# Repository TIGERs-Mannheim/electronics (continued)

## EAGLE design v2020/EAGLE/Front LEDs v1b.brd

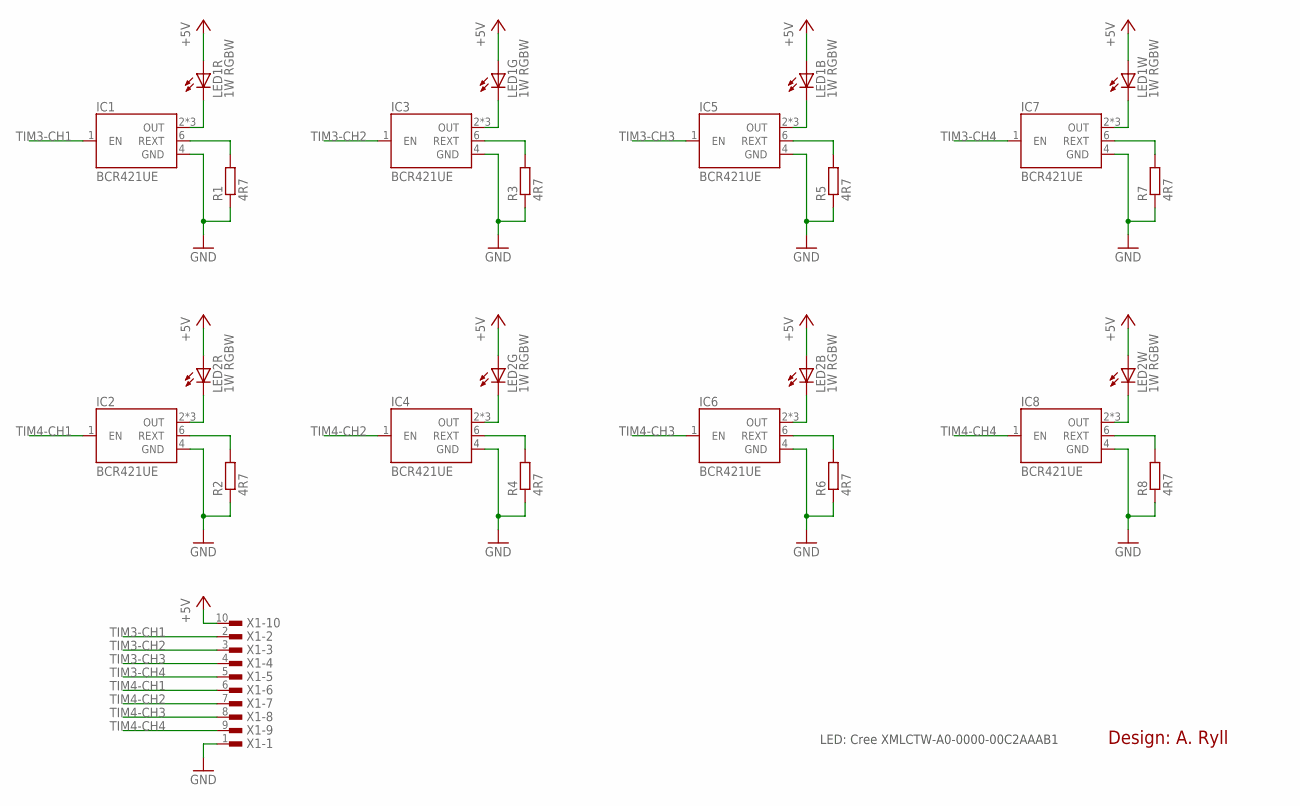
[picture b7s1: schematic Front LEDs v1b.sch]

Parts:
IC1, IC2, IC3, IC4, IC5, IC6, IC7, IC8: BCR421UE; SOT26
LED1, LED2: 1W RGBW; CREE-XLAMP; PARTNR XMLCTW-A0-0000-00C2AAAB1
R1, R2, R3, R4, R5, R6, R7, R8: 4R7; R0805
X1: TE-FPC-1MM-10H; TE-1-84952-0

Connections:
+5V: LED1.1 (A), LED1.2 (A), LED1.3 (A), LED1.4 (A), LED2.1 (A), LED2.2 (A), LED2.3 (A), LED2.4 (A), X1.10
GND: IC1.4 (GND), IC2.4 (GND), IC3.4 (GND), IC4.4 (GND), IC5.4 (GND), IC6.4 (GND), IC7.4 (GND), IC8.4 (GND), R1.1, R2.1, R3.1, R4.1, R5.1, R6.1, R7.1, R8.1, X1.1
unnamed: IC1.2 (OUT), IC1.3 (OUT), IC1.5 (OUT), LED1.8 (C)
unnamed: IC1.6 (REXT), R1.2
unnamed: IC3.2 (OUT), IC3.3 (OUT), IC3.5 (OUT), LED1.7 (C)
unnamed: IC3.6 (REXT), R3.2
unnamed: IC5.2 (OUT), IC5.3 (OUT), IC5.5 (OUT), LED1.6 (C)
unnamed: IC5.6 (REXT), R5.2
unnamed: IC7.2 (OUT), IC7.3 (OUT), IC7.5 (OUT), LED1.5 (C)
unnamed: IC7.6 (REXT), R7.2
unnamed: IC2.2 (OUT), IC2.3 (OUT), IC2.5 (OUT), LED2.8 (C)
unnamed: IC2.6 (REXT), R2.2
unnamed: IC4.2 (OUT), IC4.3 (OUT), IC4.5 (OUT), LED2.7 (C)
unnamed: IC4.6 (REXT), R4.2
unnamed: IC6.2 (OUT), IC6.3 (OUT), IC6.5 (OUT), LED2.6 (C)
unnamed: IC6.6 (REXT), R6.2
unnamed: IC8.2 (OUT), IC8.3 (OUT), IC8.5 (OUT), LED2.5 (C)
unnamed: IC8.6 (REXT), R8.2
TIM3-CH1: IC1.1 (EN), X1.2
TIM3-CH2: IC3.1 (EN), X1.3
TIM3-CH3: IC5.1 (EN), X1.4
TIM3-CH4: IC7.1 (EN), X1.5
TIM4-CH1: IC2.1 (EN), X1.6
TIM4-CH2: IC4.1 (EN), X1.7
TIM4-CH3: IC6.1 (EN), X1.8
TIM4-CH4: IC8.1 (EN), X1.9

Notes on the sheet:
Design: A. Ryll
LED: Cree XMLCTW-A0-0000-00C2AAAB1

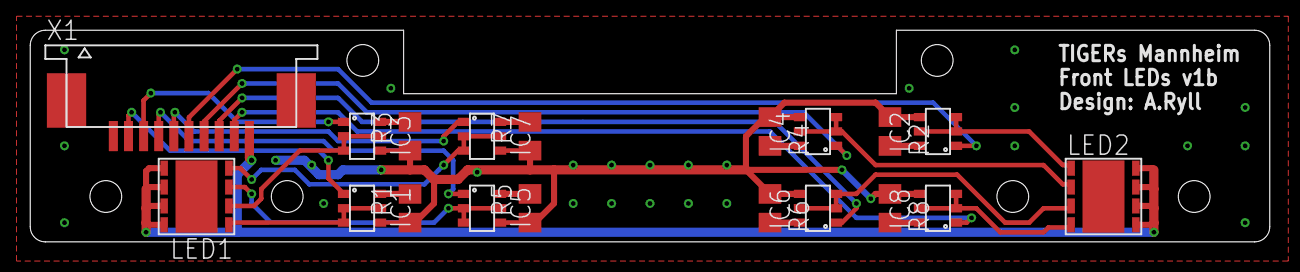
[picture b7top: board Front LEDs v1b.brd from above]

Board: 2 copper layers, 82.0 x 14.0 mm, 19 parts (0 on the bottom side), 26 nets.

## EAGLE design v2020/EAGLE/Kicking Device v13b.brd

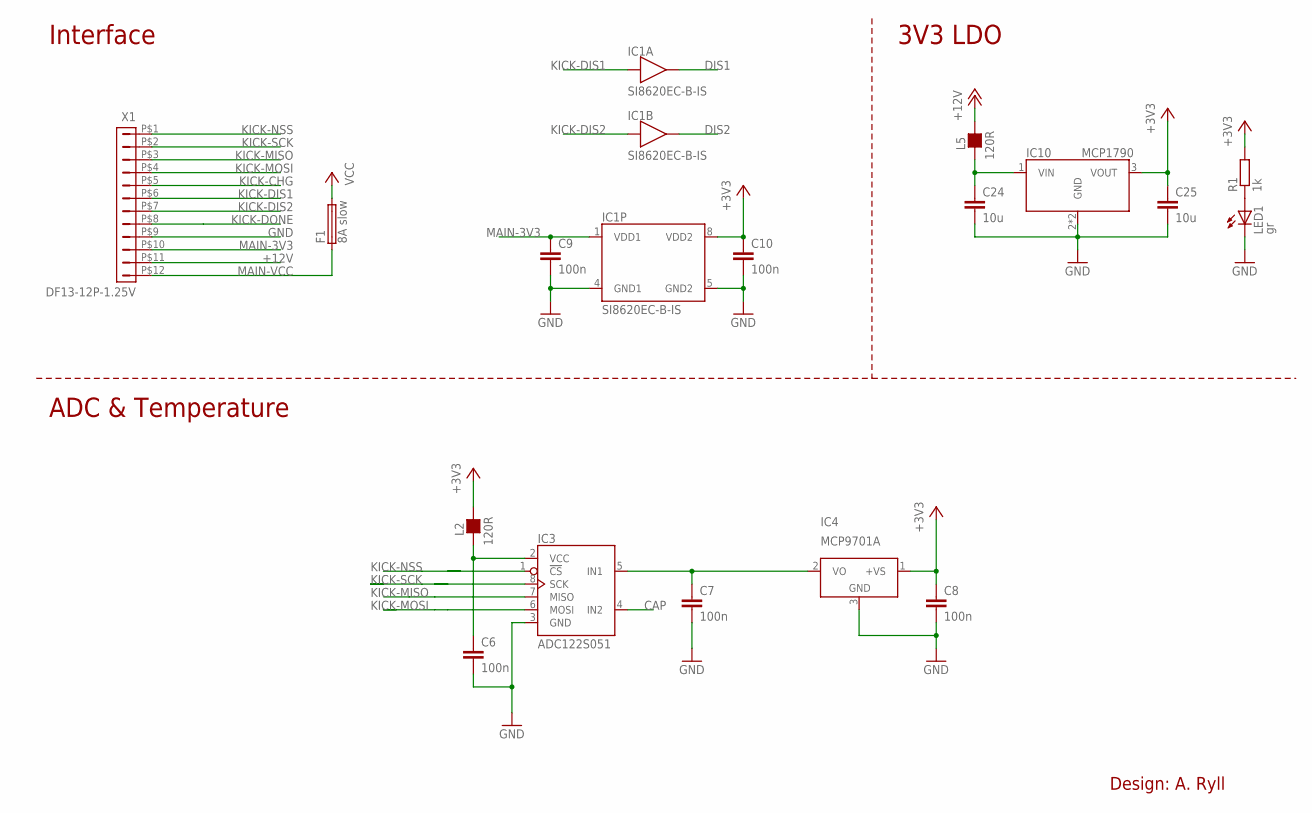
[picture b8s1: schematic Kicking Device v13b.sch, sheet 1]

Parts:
C6, C7, C8, C9, C10: 100n; C0603
C24, C25: 10u; C0603
F1: 8A slow; 1206
IC1: SI8620EC-B-IS; SOIC8N
IC3: ADC122S051; MSOP8
IC4: MCP9701A; SOT23
IC10: MCP1790; SOT223
L2, L5: 120R; L0603
LED1: gr; CHIP-LED0603
R1: 1k; R0603
X1: DF13-12P-1.25V; DF13C-12P-1.25V

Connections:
+3V3: C8.1, C10.1, C25.1, IC1.8 (VDD2), IC4.1 (+VS), IC10.3 (VOUT), L2.2, R1.2; also elsewhere on the board
+12V: L5.2, X1.P$11 (11); also elsewhere on the board
CAP: IC3.4 (IN2); also elsewhere on the board
DIS1: IC1.7 (OUT); also elsewhere on the board
DIS2: IC1.6 (OUT); also elsewhere on the board
GND: C6.2, C7.2, C8.2, C9.2, C10.2, C24.2, C25.2, IC1.4 (GND1), IC1.5 (GND2), IC3.3 (GND), IC4.3 (GND), IC10.2 (GND), IC10.4 (GND), LED1.C, X1.P$9 (9); also elsewhere on the board
KICK-CHG: X1.P$5 (5); also elsewhere on the board
KICK-DIS1: IC1.2 (IN), X1.P$6 (6)
KICK-DIS2: IC1.3 (IN), X1.P$7 (7)
KICK-DONE: X1.P$8 (8); also elsewhere on the board
KICK-MISO: IC3.7 (MISO), X1.P$3 (3)
KICK-MOSI: IC3.6 (MOSI), X1.P$4 (4)
KICK-NSS: IC3.1 (!CS), X1.P$1 (1)
KICK-SCK: IC3.8 (SCK), X1.P$2 (2)
MAIN-3V3: C9.1, IC1.1 (VDD1), X1.P$10 (10)
MAIN-VCC: F1.1, X1.P$12 (12)
unnamed: C24.1, IC10.1 (VIN), L5.1
unnamed: C6.1, IC3.2 (VCC), L2.1
unnamed: C7.1, IC3.5 (IN1), IC4.2 (VO)
unnamed: LED1.A, R1.1
VCC: F1.2; also elsewhere on the board

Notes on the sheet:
Interface
3V3 LDO
ADC & Temperature
Design: A. Ryll

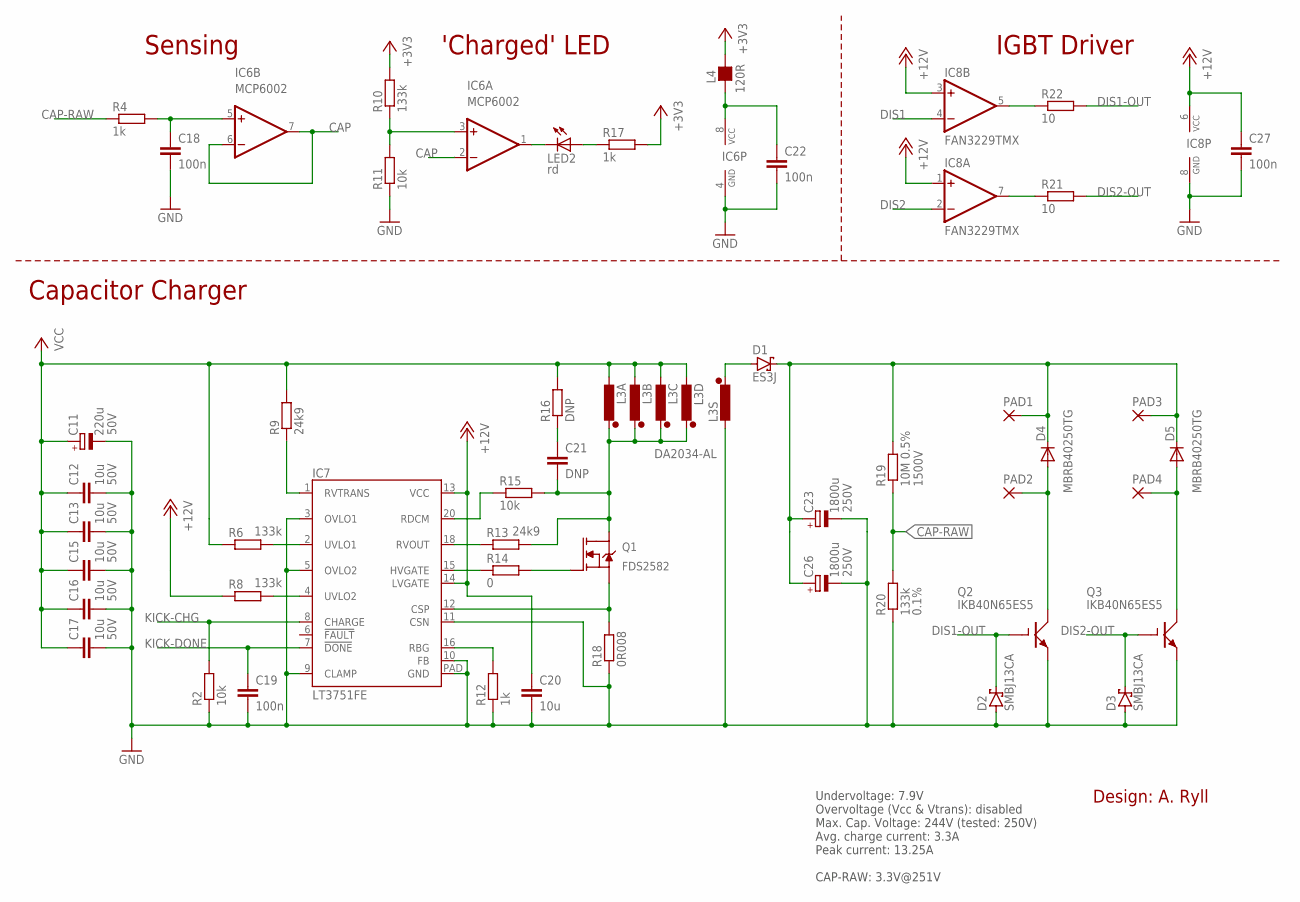
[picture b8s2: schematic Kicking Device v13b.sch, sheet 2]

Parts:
C11: 220u; PANASONIC_F; PARTNR EEEFT1H221AP
C12, C13, C15, C16, C17: 10u; C1210; PARTNR C3225X5R1H106M250AB
C18, C19, C22, C27: 100n; C0603
C20: 10u; C0603
C21: DNP; C0805
C23, C26: 1800u; EB35D
D1: ES3J; SMC
D2, D3: SMBJ13CA; SMB
D4, D5: MBRB40250TG; D2PAK
IC6: MCP6002; SOIC8N
IC7: LT3751FE; TSSOP20P
IC8: FAN3229TMX; SOIC8N
L3: DA2034-AL
L4: 120R; L0603
LED2: rd; CHIP-LED0603
PAD1, PAD2, PAD3, PAD4: WIREPAD2,54/1,0; 2,54/1,0
Q1: FDS2582; SOIC8N
Q2, Q3: IKB40N65ES5; D2PAK
R2, R11, R15: 10k; R0603
R4, R12, R17: 1k; R0603
R6, R8, R10, R20: 133k; R0603
R9, R13: 24k9; R0603
R14: 0; R1206
R16: DNP; R0805
R18: 0R008; R1206
R19: 10M 0.5%; R1206
R21, R22: 10; R1206

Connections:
+3V3: L4.2, R10.2, R17.2; also elsewhere on the board
+12V: C20.1, C27.1, IC7.13 (VCC), IC7.14 (LVGATE), IC8.1 (+IN), IC8.3 (+IN), IC8.6 (VCC), R8.1; also elsewhere on the board
CAP: IC6.2 (-IN), IC6.6 (-IN), IC6.7 (OUT); also elsewhere on the board
CAP-RAW: R4.1, R19.1, R20.2
CSP: IC7.12 (CSP), Q1.1 (S), Q1.2 (S), Q1.3 (S), R18.2
DIS1: IC8.4 (-IN); also elsewhere on the board
DIS1-OUT: D2.C, Q2.1 (G), R22.2
DIS1C: D4.1 (A), D4.3 (A), PAD2.1, Q2.2 (C)
DIS2: IC8.2 (-IN); also elsewhere on the board
DIS2-OUT: D3.C, Q3.1 (G), R21.2
DIS2C: D5.1 (A), D5.3 (A), PAD4.1, Q3.2 (C)
GND: C11.-, C12.2, C13.2, C15.2, C16.2, C17.2, C18.2, C19.2, C20.2, C22.2, C23.-, C26.-, C27.2, D2.A, D3.A, IC6.4 (GND), IC7.3 (OVLO1), IC7.5 (OVLO2), IC7.9 (CLAMP), IC7.10 (FB), IC7.11 (CSN), IC7.PAD (GND), IC8.8 (GND), L3.12 (2), Q2.3 (E), Q3.3 (E), R2.1, R11.1, R12.1, R18.1, R20.1; also elsewhere on the board
KICK-CHG: IC7.8 (CHARGE), R2.2; also elsewhere on the board
KICK-DONE: C19.1, IC7.7 (!DONE); also elsewhere on the board
LOUT: D1.A, L3.1
unnamed: IC8.7 (OUT), R21.1
unnamed: IC8.5 (OUT), R22.1
unnamed: C22.1, IC6.8 (VCC), L4.1
unnamed: IC6.3 (+IN), R10.1, R11.2
unnamed: C18.1, IC6.5 (+IN), R4.2
unnamed: LED2.A, R17.1
unnamed: IC6.1 (OUT), LED2.C
unnamed: IC7.16 (RBG), R12.2
unnamed: C21.1, R16.1
unnamed: Q1.4 (G), R14.2
unnamed: IC7.15 (HVGATE), R14.1
unnamed: IC7.18 (RVOUT), R13.1
unnamed: IC7.20 (RDCM), R15.1
unnamed: IC7.1 (RVTRANS), R9.1
unnamed: IC7.2 (UVLO1), R6.2
unnamed: IC7.4 (UVLO2), R8.2
VCAP: C23.+, C26.+, D1.C, D4.2 (C), D5.2 (C), PAD1.1, PAD3.1, R19.2
VCC: C11.+, C12.1, C13.1, C15.1, C16.1, C17.1, L3.3 (2), L3.4 (2), L3.5 (2), L3.6 (2), R6.1, R9.2, R16.2; also elsewhere on the board
VDRAIN: C21.2, L3.7 (1), L3.8 (1), L3.9 (1), L3.10 (1), Q1.5 (D), Q1.6 (D), Q1.7 (D), Q1.8 (D), R13.2, R15.2

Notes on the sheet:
Sensing
'Charged' LED
IGBT Driver
Undervoltage: 7.9V Overvoltage (Vcc & Vtrans): disabled Max. Cap. Voltage: 244V (tested: 250V) Avg. charge current: 3.3A Peak current: 13.25A
CAP-RAW: 3.3V@251V
Capacitor Charger
Design: A. Ryll

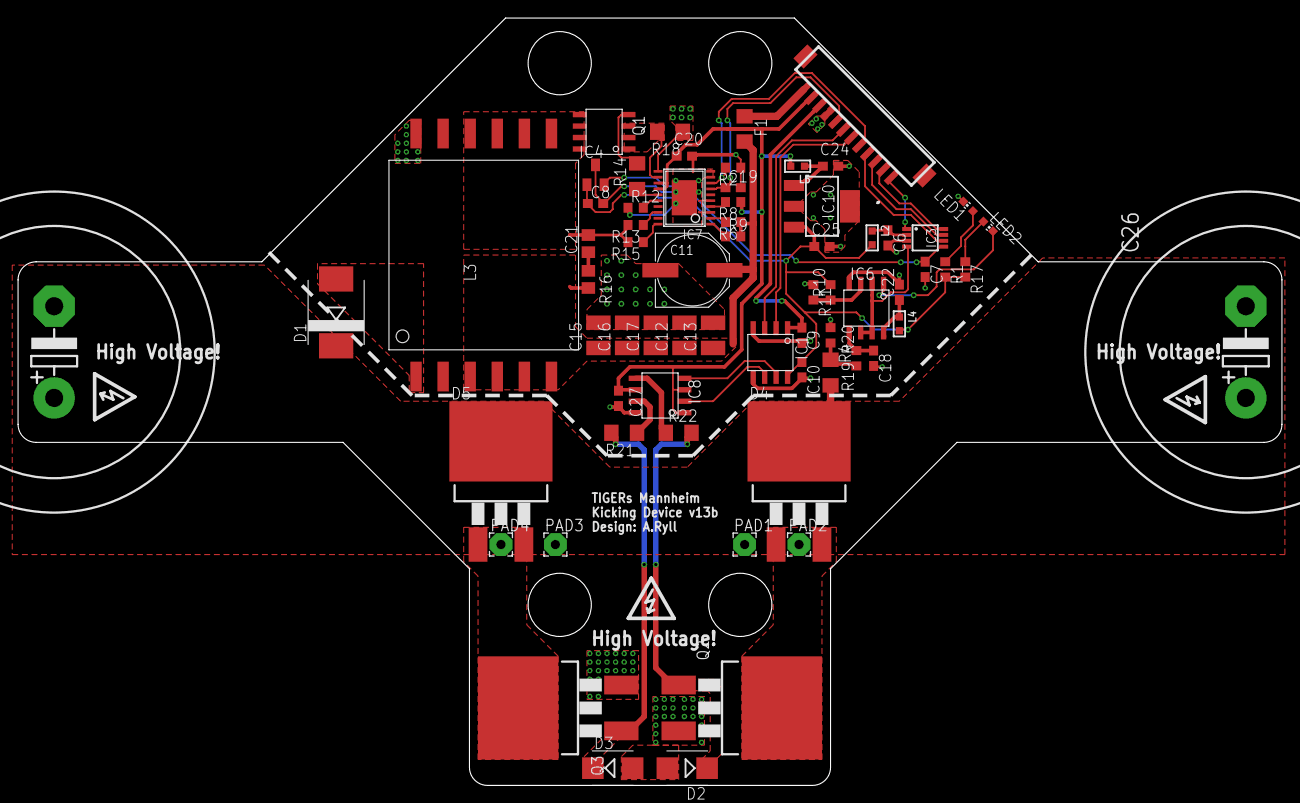
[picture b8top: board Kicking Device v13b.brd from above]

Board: 2 copper layers, 140.0 x 85.0 mm, 67 parts (0 on the bottom side), 46 nets.

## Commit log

2020-04-14 Release files for v2020 electronics
2020-04-17 Update LICENSE
2025-07-08 Added project files for KiCad9 converted from EAGLE
